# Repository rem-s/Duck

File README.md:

# Duck Project

Duck is a project that make own robots moving just like a duck.

- It follows a robot in front of itself.
- It follows sound comes from a parent robot and move towards that direction.

## Description

In this project, we have made components of duck by ourself.

Hardware level

- Wireless-controller
- Circuit design
- 3D model
- Sensor control
  
Software level

- GUI
- image recognition
- voice recognition

## Demo

This is a tracking demo

## Requirement

- python 3.6
- tensorflow 1.40
- pyqt

## Usage

python main.py

## Contribution

## Licence

## Author

REMs[https://github.com/rem-s/Duck]

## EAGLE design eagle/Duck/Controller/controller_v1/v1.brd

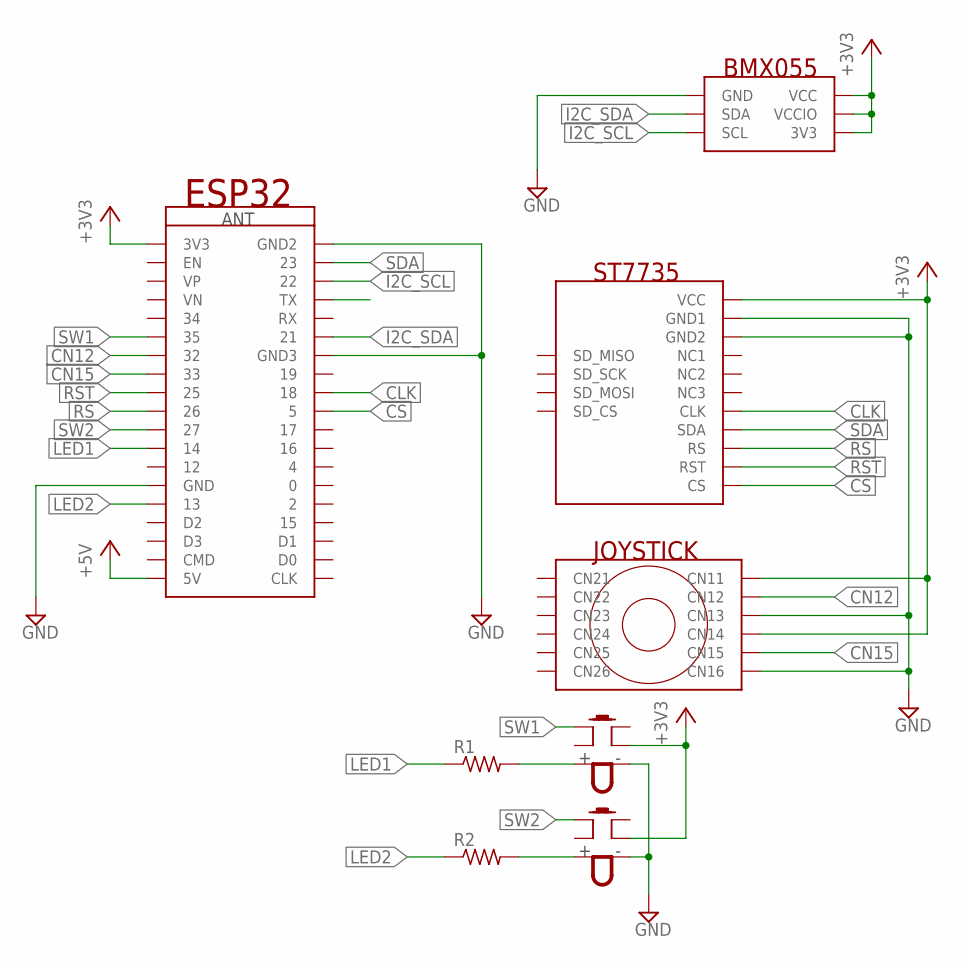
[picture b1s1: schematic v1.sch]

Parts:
R1, R2: R-US_0309/12; 0309/12
U$1: ST7735
U$2: JOYSTICK
U$3: ESP32
U$4, U$5: PUSH_SW_LED
U$6: BMX055

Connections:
+3V3: U$1.VCC, U$2.CN11, U$2.CN14, U$3.3V3, U$4.P$6 (P4), U$5.P$6 (P4), U$6.3V3, U$6.VCC, U$6.VCCIO
+5V: U$3.5V
CLK: U$1.CLK, U$3.18
CN12: U$2.CN12, U$3.32
CN15: U$2.CN15, U$3.33
CS: U$1.CS, U$3.5
GND: U$1.GND1, U$1.GND2, U$2.CN13, U$2.CN16, U$3.GND, U$3.GND2, U$3.GND3, U$4.P$4 (PO), U$5.P$4 (PO), U$6.GND
I2C_SCL: U$3.22, U$6.SCL
I2C_SDA: U$3.21, U$6.SDA
LED1: R1.1, U$3.14
LED2: R2.1, U$3.13
unnamed: R1.2, U$4.P$3 (PI)
unnamed: R2.2, U$5.P$3 (PI)
RS: U$1.RS, U$3.26
RST: U$1.RST, U$3.25
SDA: U$1.SDA, U$3.23
SW1: U$3.35, U$4.P$1 (P1)
SW2: U$3.27, U$5.P$1 (P1)

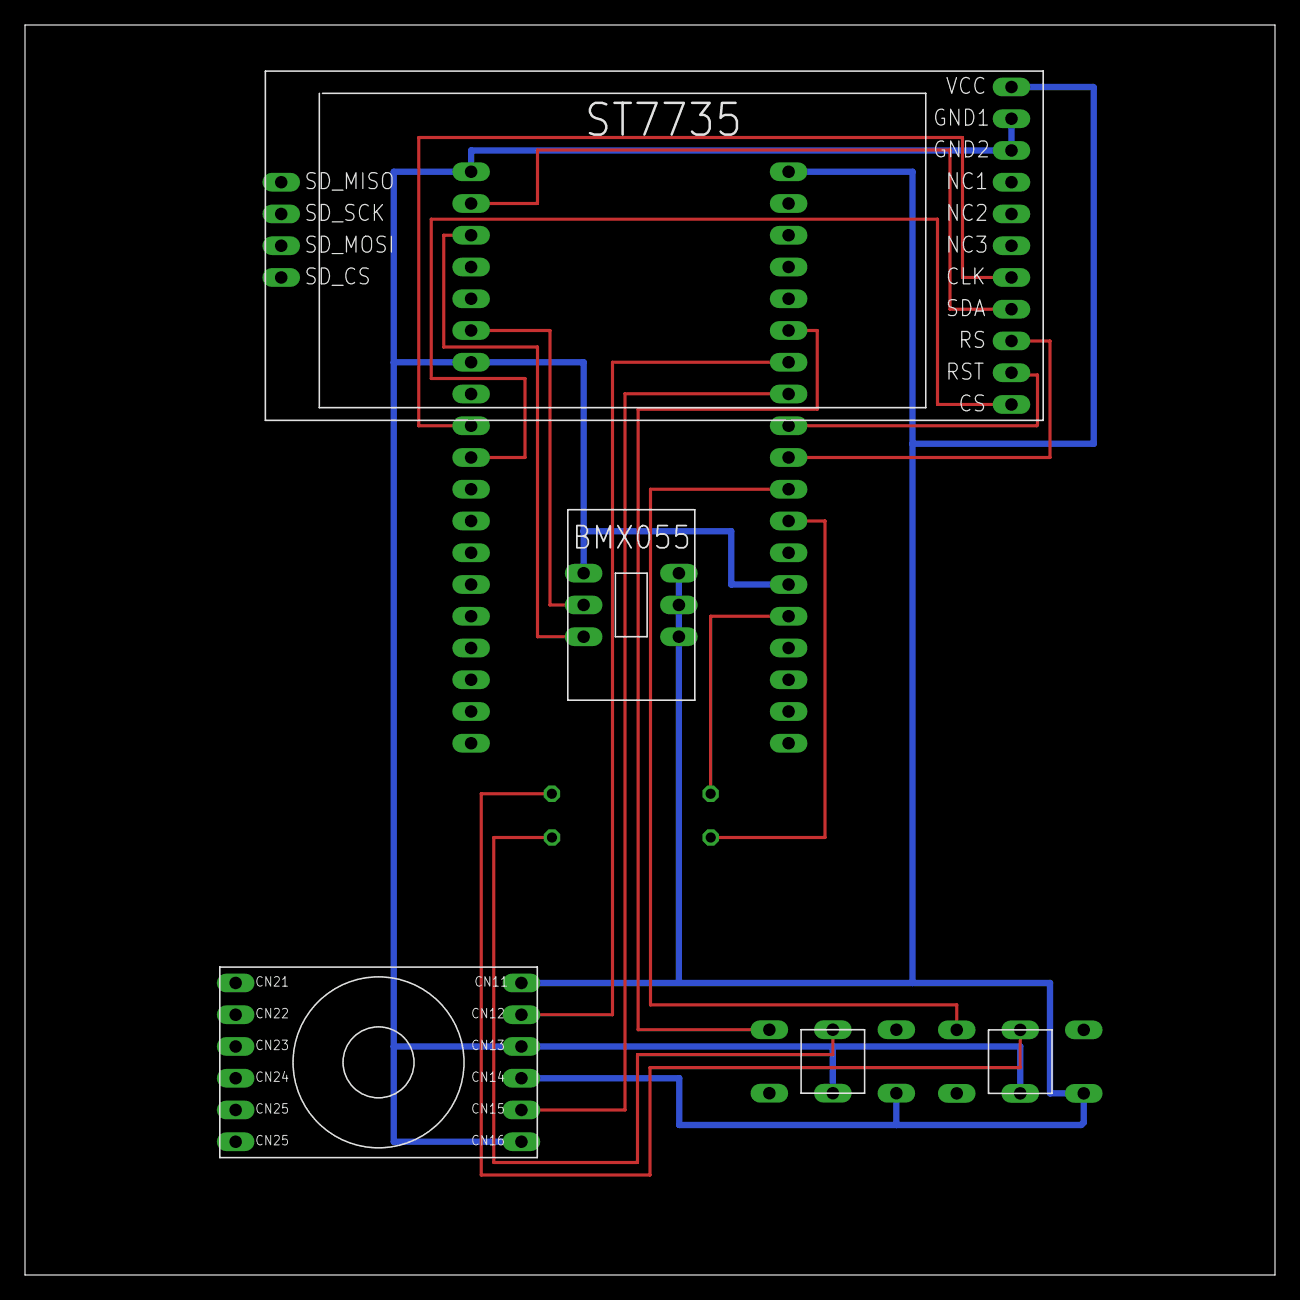
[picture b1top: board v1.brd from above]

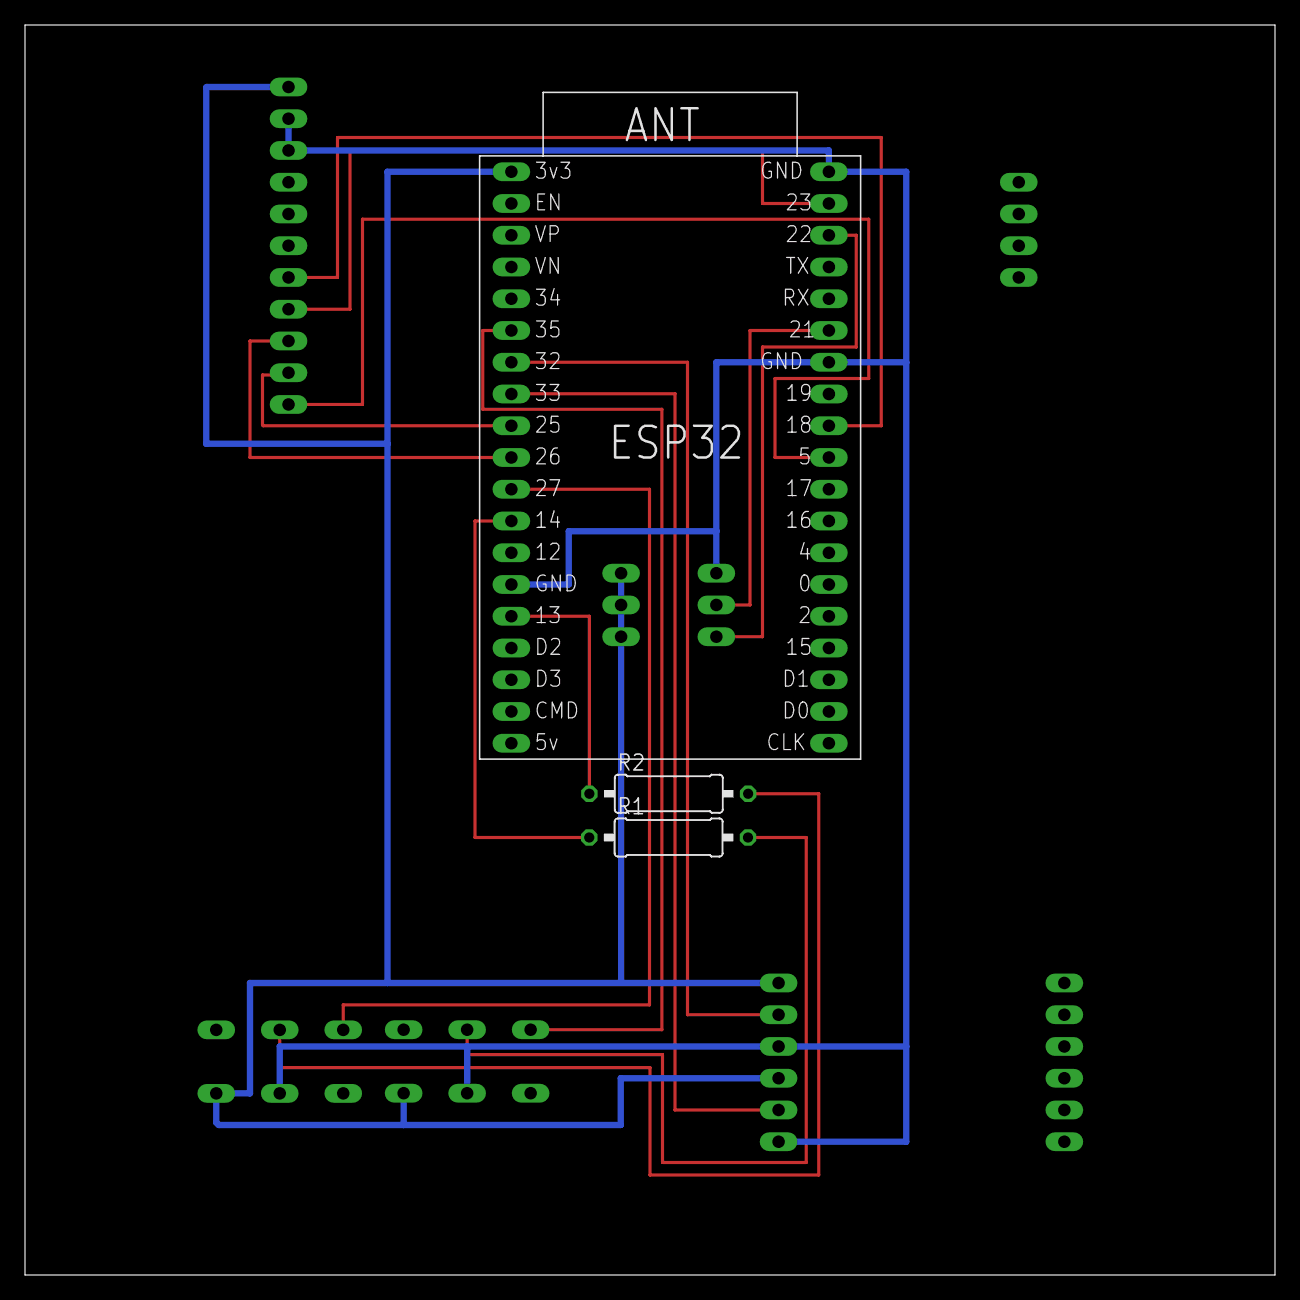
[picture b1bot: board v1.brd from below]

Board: 2 copper layers, 100.0 x 100.0 mm, 8 parts (3 on the bottom side), 17 nets.

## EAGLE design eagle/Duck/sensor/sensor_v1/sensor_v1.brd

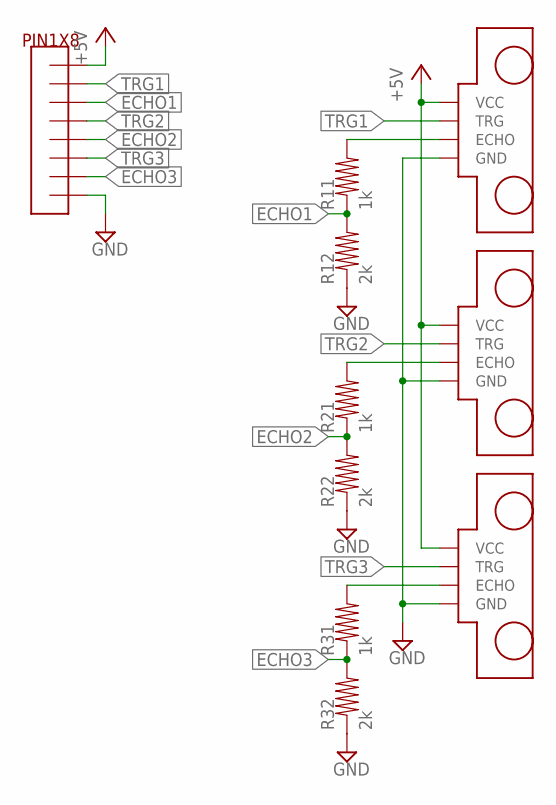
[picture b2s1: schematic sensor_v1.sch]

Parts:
R11, R21, R31: 1k; SMD_REG0805
R12, R22, R32: 2k; SMD_REG0805
U$1, U$2, U$3: HCSR04
U$4: PIN1X8_254

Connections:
+5V: U$1.VCC, U$2.VCC, U$3.VCC, U$4.P$1 (P1)
ECHO1: R11.P1, R12.P2, U$4.P$3 (P3)
ECHO2: R21.P1, R22.P2, U$4.P$5 (P5)
ECHO3: R31.P1, R32.P2, U$4.P$7 (P7)
GND: R12.P1, R22.P1, R32.P1, U$1.GND, U$2.GND, U$3.GND, U$4.P$8 (P8)
unnamed: R21.P2, U$2.ECHO
unnamed: R11.P2, U$1.ECHO
unnamed: R31.P2, U$3.ECHO
TRG1: U$1.TRG, U$4.P$2 (P2)
TRG2: U$2.TRG, U$4.P$4 (P4)
TRG3: U$3.TRG, U$4.P$6 (P6)

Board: 2 copper layers, 10 parts (1 on the bottom side), 11 nets, no tracks yet.

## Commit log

2019-03-31 home sweet home
2019-03-31 Revert "home sweet home"
    This reverts commit 92a2e7eeffe5c6453772d2ef142139bf22ab9b22.
2019-11-24 archive 2019-11
2020-01-12 ADD eagle file
2020-01-24 record_and_mfcc_functionality
2020-01-25 sequensive_record
2020-02-16 ADD serialbt
2020-02-16 get_mfcc_and_inference
2020-03-03 add first project
2020-03-07 add mic_interface
2020-03-07 add udp and motor ta7291p
2020-03-07 FIRST COMMITgit add .
2020-03-07 add main.py
2020-03-07 add class MFCC
2020-03-07 second commit
2020-03-07 third comit
2020-03-07 add wifi connecting feature
2020-03-07 t sh
2020-03-07 firth commit
2020-03-08 add model directory and main.py, dataset
2020-03-13 remove argument from init_wifi
2020-03-13 rename name var
2020-03-14 edit control and network
2020-03-14 add PC program
2020-03-15 UDP succeededededededed
2020-03-15 add additional mic and model and AI dir and so on
2020-03-16 CREATE::sensor.ino
2020-03-17 change pin
2020-03-17 fix path includes.
2020-03-17 nightly commit
2020-03-19 add TCP communication
2020-03-20 commit camera.py
2020-03-20 add cam.py
2020-03-20 1024
2020-03-20 Shinchoku
2020-03-20 home made Shinchoku
2020-03-20 test commit
2020-03-20 Joystick test code
2020-03-20 Shinchoku, home made.
2020-03-21 add image processing
2020-03-21 commit cam
2020-03-22 a∂∂ LCD test
2020-03-28 data collect.py
2020-03-28 add img collect python
2020-03-28 add img collect
2020-03-28 add complete
2020-03-28 change image
2020-03-28 LCD Test Programme
2020-03-28 commit image
2020-03-28 add eagle
2020-03-29 renew sensor.py
2020-03-29 h m sch
2020-03-29 fix typo
2020-03-29 add real-time voice plot
2020-03-29 lcd sh
2020-03-29 remove passphrase string
2020-04-01 board design
2020-04-04 add multiple window
2020-04-05 renew sonar.py
2020-04-05 add line detection
2020-04-06 nothing to commit for now
2020-04-12 test sonar
2020-04-18 modified acc.py (doesn't use Adafruit)
2020-04-18 removed acc.py and modified adxl345.py
2020-04-18 return acc result as list
2020-04-18 I am a jellyfish.
2020-04-19 final set pin number
2020-04-19 make code more clean but not stable somehow
2020-04-19 Upside down
2020-04-19 wiring finished
    but refactoring needed.
2020-04-25 elegance
2020-05-03 temporary finish linetrace
2020-05-03 raspberry pi branch
2020-05-04 NightlyCanary
2020-05-04 NightlyCanary
    lower to UPPER, defined constant
2020-05-04 NightlyCanary
    Change format of serial output
2020-05-04 NightlyCanary
    fix typo
2020-05-04 NightlyCanary
    add comment
2020-05-09 finished
2020-05-09 Update lcd_init.h
    Change display rotation to 0 degree to adapt to board
2020-05-09 Remove .DS_Store
    added to .gitignore
2020-05-09 Update wifi_ducks.h
    lower to UPPER, Definition "SSID_WIFIS"
2020-05-09 Add temp.py
2020-05-09 Fix Display rotation
    display rotation is always 1
2020-05-09 Update button.h
    Use pulldown
2020-05-09 add test programs and refined main app program
2020-05-09 Nightly Backup
2020-05-10 Anable to calcurate distance using temperature sensor
2020-05-10 Debug wifi init
    remove for
2020-05-10 Debug wifi init
    print ssid at disp_nw
2020-05-11 Create gyro.h
    and refactor
2020-05-23 correct image window and voice window
2020-05-24 linetrace
2020-05-24 backup
2020-05-24 modified some parts in PC/control/models
2020-05-24 qtshow
2020-05-24 linetrace.py
2020-05-24 konami code
2020-05-31 last commit
2020-06-07 demo1
2020-06-07 checkout
2020-06-15 first demo
2020-07-12 re-struct directories and add speaker recognition model
2020-07-13 modified PC/speaker_test.py and PC/control/sensor/mic.py
2020-08-02 add speaker verification code
2020-09-08 edit readme and add gif file
2020-09-08 create 'media' branch and add gif
2020-09-08 edit readme
2020-10-18 ReShinchoku
2020-10-18 tcp hobo done
2020-10-25 works
2020-11-29 add gui for source_direction
2020-11-30 Add gui for source localize hist
2020-11-30 Add sound source localization gui more simple one
2020-12-01 Add sound source localize
2020-12-02 master ogaki
